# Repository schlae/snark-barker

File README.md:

# The Snark Barker - a SB 1.0 Clone

The Snark Barker is a 100% compatible clone of the famed SB 1.0 "Killer Card"
sound card from 1989. It implements all the features, including the digital
sound playback and recording, Ad Lib compatible synthesis, the joystick/MIDI
port, and the CMS chips (which are actually Philips SAA1099 synthesizer
devices).

All of the components are readily available. In the bill of materials,
Mouser part numbers are listed where they are available. Chips not available
from Mouser can be purchased from a variety of sources in China.

[Schematic](https://github.com/schlae/snark-barker/blob/master/SnarkBarker.pdf)

[Bill of Materials](https://github.com/schlae/snark-barker/blob/master/SnarkBarker.csv)

Please note that the 0.1" header pins are *not* listed on the BOM. They are
standard breakaway headers (both single and double row). Jumper shunts are
also not listed on the BOM.

[Fab files](https://github.com/schlae/snark-barker/blob/master/fab/SnarkBarker.zip)

Board dimensions are 9.1 x 4.2 inches. When ordering the board, you may want
to specify a card edge bevel (fairly cheap!) and selective gold plating
(expensive!) depending on your needs. The soldermask color can be whatever
you like, but hot pink is preferred.

## The Volume Knob
There don't seem to be any off-the-shelf knobs compatible with the Alps
potentiometer. You may be able to 3D print one based on the model below.
I'd recommend using a high-resolution SLA printer like the Formlabs Form 2.

Fasten it to the potentiometer using an M1.4x0.3mm thread, 6mm long screw
(McMaster-Carr part number 91800A036 or equivalent).

[Volume knob STEP model](https://github.com/schlae/snark-barker/blob/master/mech/vol_knob.zip)

Update: I've added a modified volume knob that may print better on FDM
printers.

[Volume knob STEP model, FDM version](https://github.com/schlae/snark-barker/blob/master/mech/vol_knob_fdm.zip)

## The ISA Card Bracket
The bracket specified in the BOM is a blank Keystone 9200 bracket. You will
need to punch or drill holes for the connectors. The KiCad board file has
detailed dimensions showing where to make the holes in the bracket.

I use a chassis nibbler tool to make the square slot for the volume knob as
well as the hole for the DA-15 joystick/MIDI connector. If you are rich,
Greenlee makes a punch for the DA-15 outline.

## The Firmware
There are two ways to get a programmed 80C51 chip for the Snark Barker. One
is to purchase a SB 2.0 DSP chip from China and put it in a 44-PLCC to
40-DIP adapter. This works fine and provides the largest feature set.

Another option is to buy a blank Atmel 89S51 (as listed in the BOM) and
program it with [this HEX file](https://github.com/schlae/snark-barker/blob/master/firmware/sb.hex).

## Assembly Notes
You may wish to socket the two CMS chips, the 80C51 microcontroller, and the
two Yamaha chips.

Be sure to add the 4.7K ohm bodge resistor on top of U5, running between
pins 4 and 14. (Shown below.)

For MIDI to work properly, you'll need to solder jumper wires on the headers
marked TXD and RXD (next to the SNARK BARKER logo). Originally these two 3-pin
headers may have been used as a debug port.

Be sure to place shunts in the jumpers marked DRQ1 and JP1, to enable DMA and
the joystick, respectively. Also place shunts to configure the I/O address and
IRQ.

## Testing and Diagnostics
Test your shiny new card using your favorite PC games, or use the [SBDIAG
program that I've written](https://github.com/schlae/snark-barker/tree/master/sbdiag).

## Other Notes
Like the original SB 1.0, the Snark Barker does not need a -5V rail.

## License
This work is licensed under a Creative Commons Attribution-ShareAlike 4.0
International License. See [https://creativecommons.org/licenses/by-sa/4.0/](https://creativecommons.org/licenses/by-sa/4.0/).

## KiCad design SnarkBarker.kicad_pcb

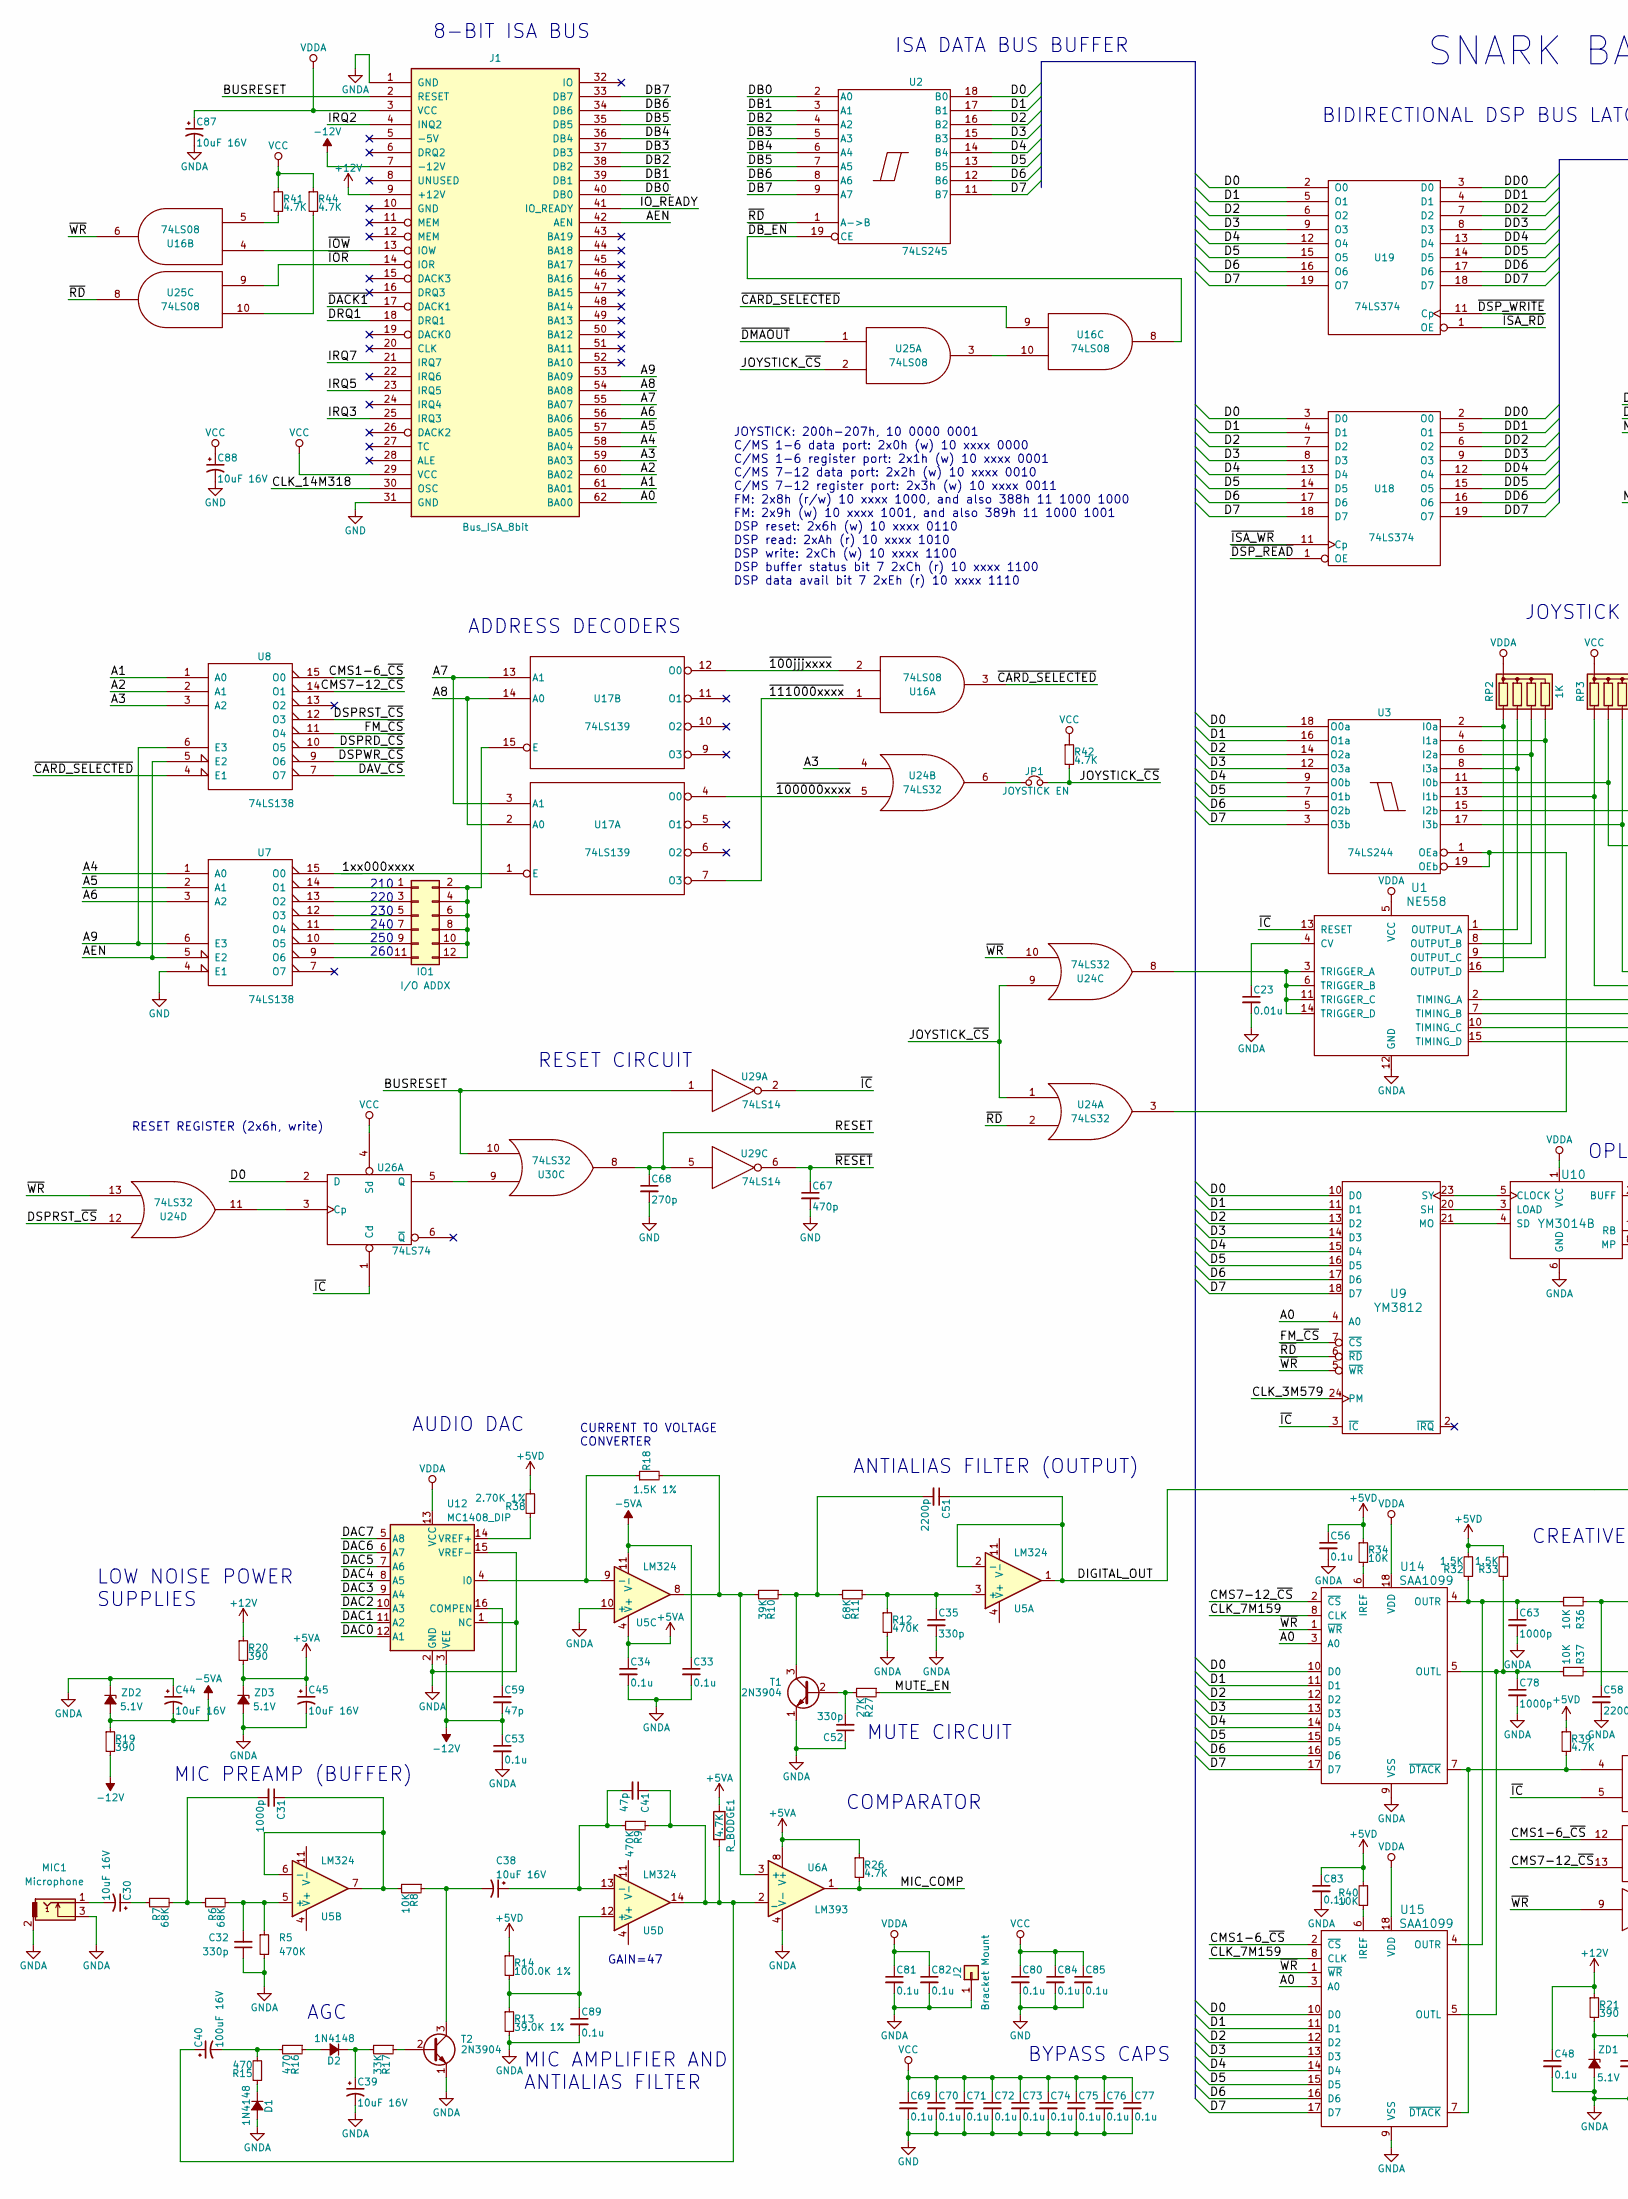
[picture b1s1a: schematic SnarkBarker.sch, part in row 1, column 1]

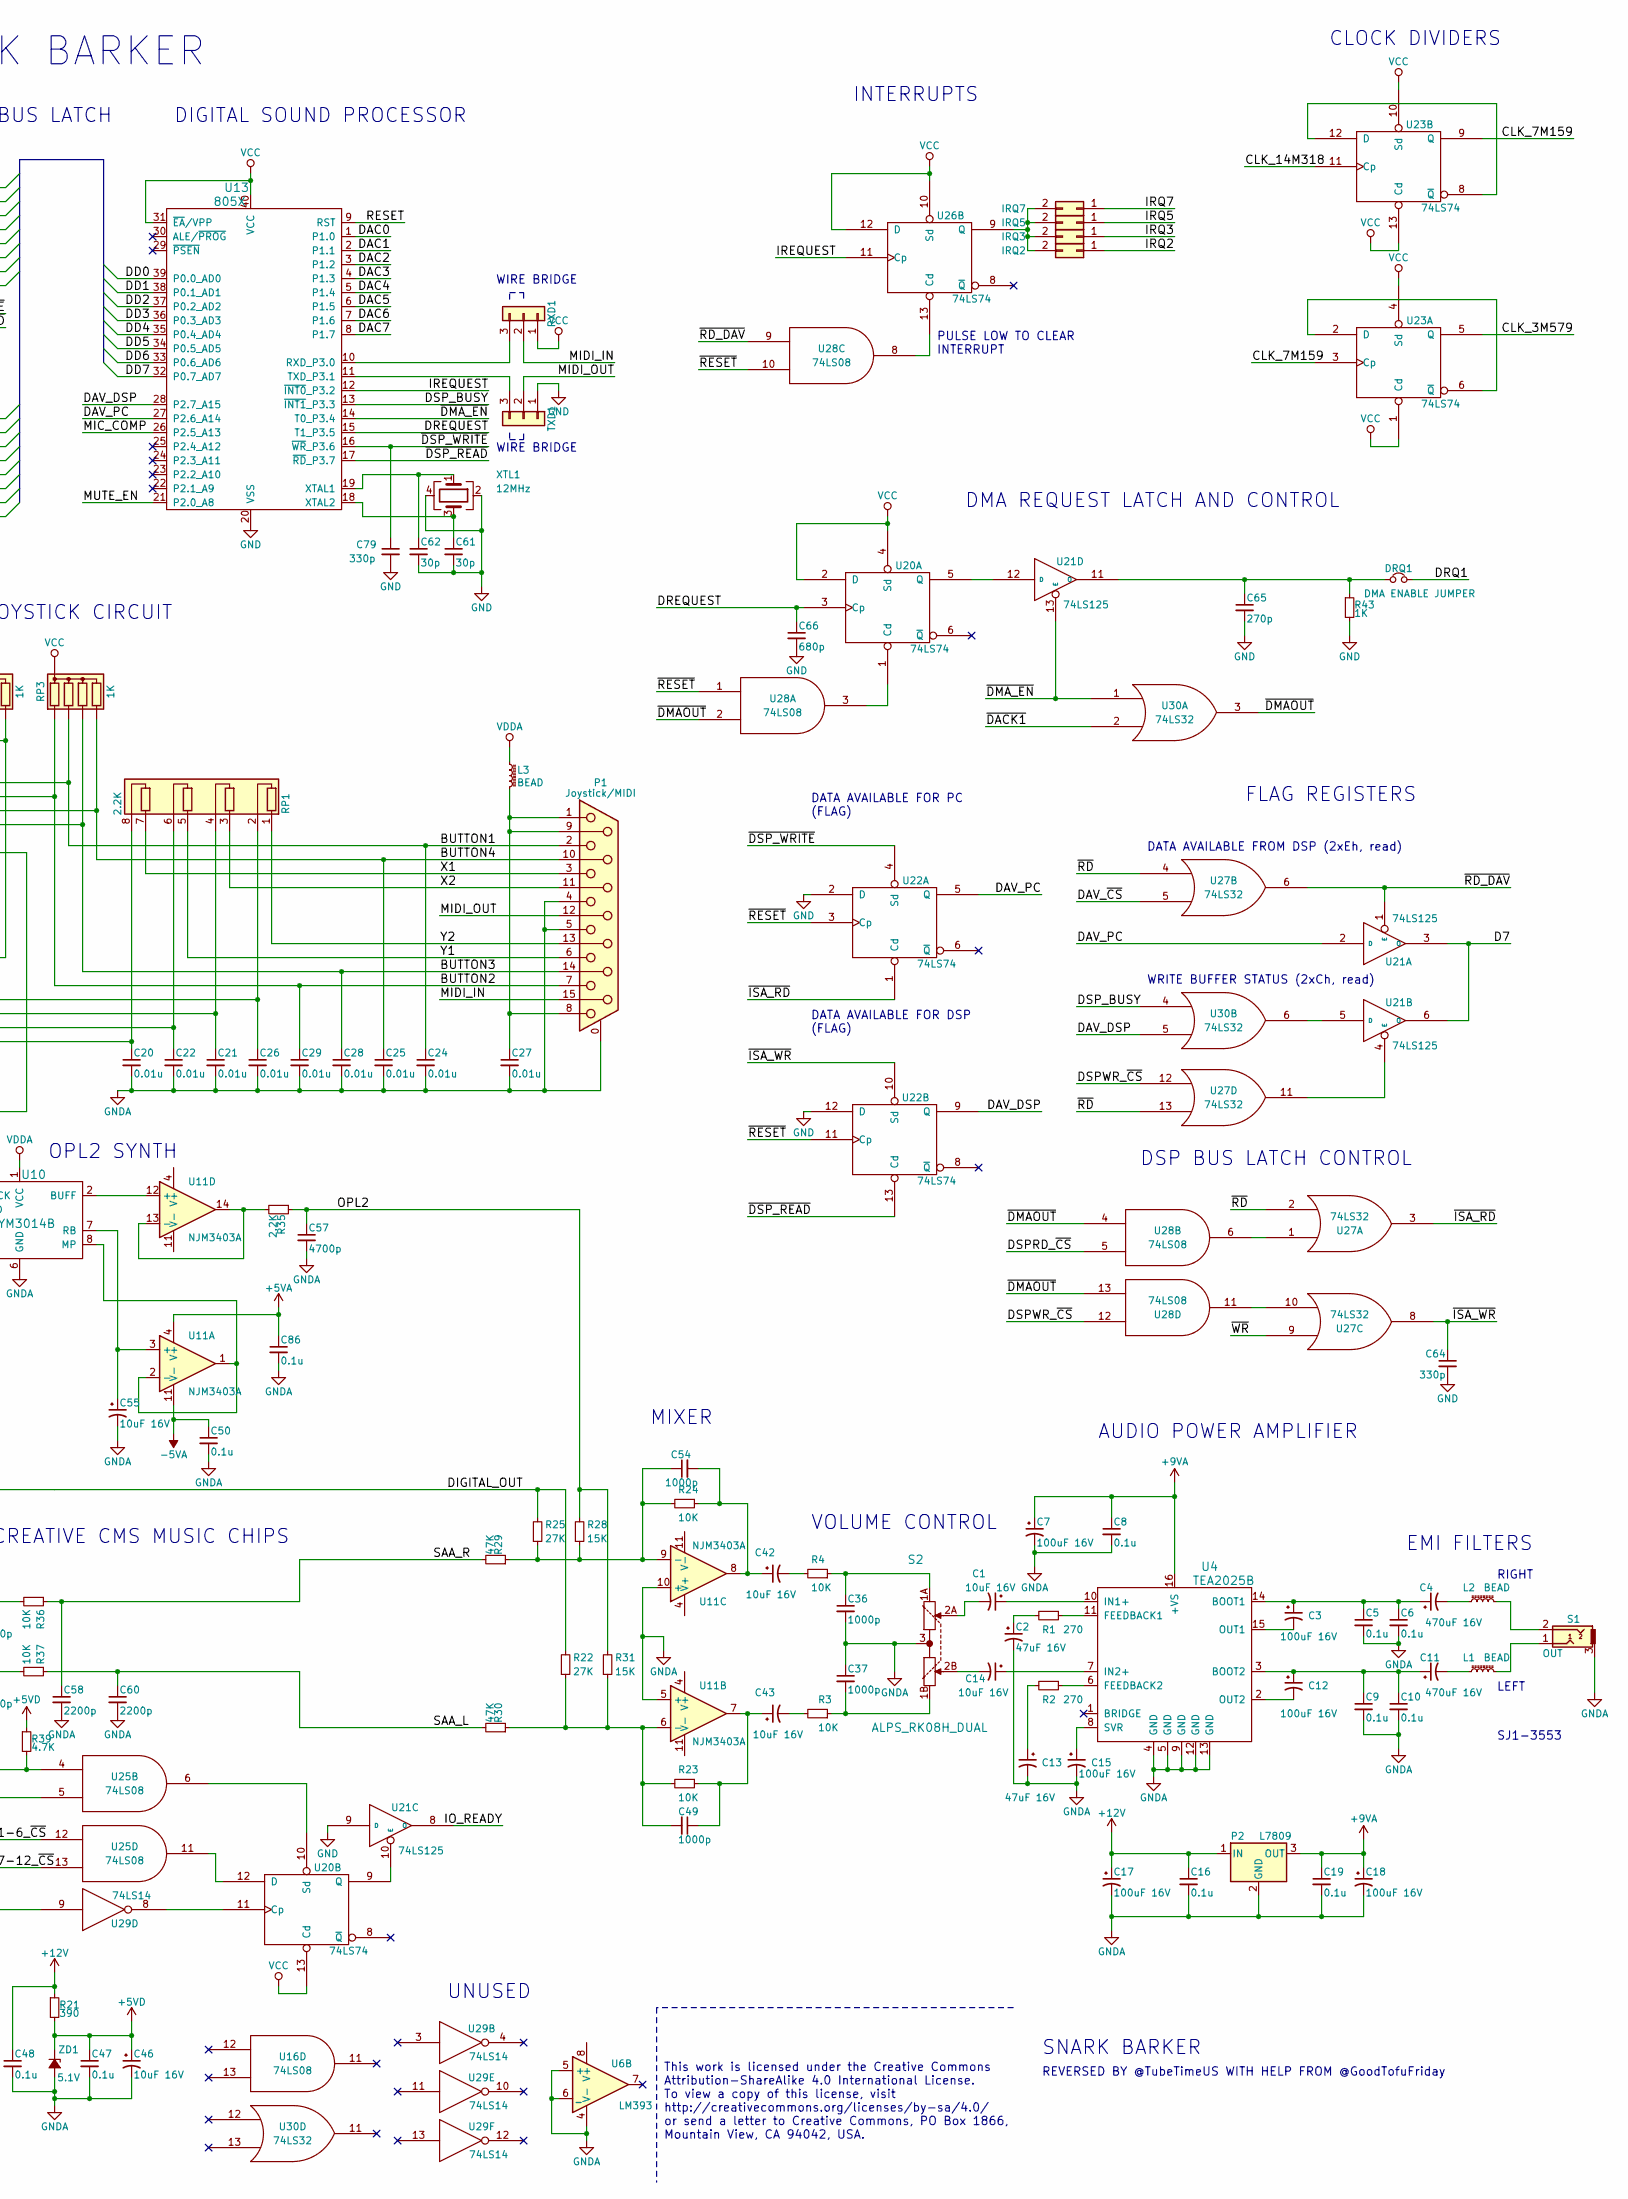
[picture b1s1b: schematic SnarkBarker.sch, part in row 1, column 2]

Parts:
C1, C14, C30, C38, C39, C42, C43, C44, C45, C46, C55, C87, C88: 10uF 16V; SB_C_RADIAL_75_150; Mouser 667-ECA-1CM100I
C2, C13: 47uF 16V; SB_C_RADIAL_75_150; Mouser 667-ECA-1CM470I
C3, C7, C12, C15, C17, C18, C40: 100uF 16V; SB_C_RADIAL_100_320; Mouser 667-ECA-1CM101I
C4, C11: 470uF 16V; SB_C_RADIAL_100_320; Mouser 667-ECA-1CM471B
C5, C6, C8, C9, C10, C16, C19, C33, C34, C47, C48, C50, C53, C56, C69, C70, C71, C72, C73, C74, C75, C76, C77, C80, C81, C82, C83, C84, C85, C86, C89: 0.1u; SB_C_AXIAL_275; Mouser 581-SA105E104M
C20, C21, C22, C23, C24, C25, C26, C27, C28, C29: 0.01u; SB_C_DISC_200; Mouser 810-FG28X7R1H103KNT0
C31, C36, C37, C49, C54, C63, C78: 1000p; SB_C_DISC_200; Mouser 810-FG28X7R1H102KNT6
C32, C35, C52, C64, C79: 330p; SB_C_DISC_200; Mouser 810-FG28C0G1H331JNT6
C41, C59: 47p; SB_C_DISC_200; Mouser 810-FG28C0G1H470JNT6
C51, C58, C60: 2200p; SB_C_DISC_200; Mouser 810-FG28X7R1H222KNT6
C57: 4700p; SB_C_DISC_200; Mouser 810-FG28C0G1H472JNT6
C61, C62: 30p; SB_C_DISC_200; Mouser 810-FG28C0G1H270JNT6
C65, C68: 270p; SB_C_DISC_200; Mouser 810-FG28C0G1H271JNT0
C66: 680p; SB_C_DISC_200; Mouser 810-FG28C0G1H681JNT6
C67: 470p; SB_C_DISC_200; Mouser 810-FG28C0G1H471JNT6
D1, D2: 1N4148; SB_D_AXIAL_400; Mouser 512-1N4148
DRQ1: DMA ENABLE JUMPER; SB_HDR_1X2
IO1: I/O ADDX; SB_HDR_2X6
IRQ2, IRQ3, IRQ5, IRQ7: Conn_02x01; SB_HDR_1X2
J1: Bus_ISA_8bit; BUS_PC
J2: Bracket Mount; SB_MH_125; Mouser 534-9200
JP1: JOYSTICK EN; SB_HDR_1X2
L1, L2, L3: BEAD; SB_L_AXIAL_500; Mouser 623-2743004111
MIC1: Microphone; SB_MJ-3536N; Mouser 490-MJ-3536N
P1: Joystick/MIDI; SB_DB15_152-3415; Mouser 152-3415
P2: L7809; SB_TO220; Mouser 511-L7809CV
R1, R2: 270; SB_R_AXIAL_400; Mouser 603-CFR-25JB-52-270R
R3, R4, R8, R23, R24, R34, R36, R37, R40: 10K; SB_R_AXIAL_400; Mouser 603-CFR-25JB-52-10K
R5, R9, R12: 470K; SB_R_AXIAL_400; Mouser 603-CFR-25JR-52470K
R6, R7, R11: 68K; SB_R_AXIAL_400; Mouser 603-CFR-25JB-52-68K
R10: 39K; SB_R_AXIAL_400; Mouser 603-CFR-25JB-52-39K
R13: 39.0K 1%; SB_R_AXIAL_400; Mouser 603-MFR-25FBF52-39K
R14: 100.0K 1%; SB_R_AXIAL_400; Mouser 603-MFR-25FBF52-100K
R15, R16: 470; SB_R_AXIAL_400; Mouser 603-CFR-25JB-52-470R
R17: 33K; SB_R_AXIAL_400; Mouser 603-CFR-25JB-52-33K
R18: 1.5K 1%; SB_R_AXIAL_400; Mouser 603-MFR-25FBF52-1K5
R19, R20, R21: 390; SB_R_AXIAL_400; Mouser 603-CFR-25JB-52-390R
R22, R25, R27: 27K; SB_R_AXIAL_400; Mouser 603-CFR-25JB-52-27K
R26, R39, R41, R42, R44: 4.7K; SB_R_AXIAL_400; Mouser 603-CFR-25JB-52-4K7
R28, R31: 15K; SB_R_AXIAL_400; Mouser 603-CFR-25JB-52-15K
R29, R30: 47K; SB_R_AXIAL_400; Mouser 603-CFR-25JB-52-47K
R32, R33: 1.5K; SB_R_AXIAL_400; Mouser 603-CFR-25JB-52-1K5
R35: 2.2K; SB_R_AXIAL_400; Mouser 603-CFR-25JB-52-2K2
R38: 2.70K 1%; SB_R_AXIAL_400; Mouser 603-MFR-25FBF52-2K7
R43: 1K; SB_R_AXIAL_400; Mouser 603-CFR-25JR-521K
RP1: 2.2K; SB_RP_4B; Mouser 652-4608X-AP2-222LF
RP2, RP3: 1K; SB_RP_4C; Mouser 652-4605X-AP1-102LF
RXD1: Conn_01x03; SB_HDR_1X3
R_BODGE1: 4.7K; Mouser 603-CFR-25JB-52-4K7
S1: OUT; SB_SJ1-3553; Mouser 490-SJ1-3553NG
S2: ALPS_RK08H_DUAL; SB_ALPS_RK08_DUAL; Mouser 688-RK08H12100F3
T1, T2: 2N3904; SB_TO92; Mouser 833-2N3904-AP
TXD1: Conn_01x03; SB_HDR_1X3
U1: NE558; SB_DIP16_300
U2: 74LS245; SB_DIP20_300; Mouser 595-SN74LS245N
U3: 74LS244; SB_DIP20_300; Mouser 595-SN74LS244N
U4: TEA2025B; SB_DIP16_300
U5: LM324; SB_DIP14_300; Mouser 512-LM324AN
U6: LM393; SB_DIP8_300; Mouser 595-LM393P
U7, U8: 74LS138; SB_DIP16_300; Mouser 595-SN74LS138NE4
U9: YM3812; SB_DIP24_600
U10: YM3014B; SB_DIP8_300
U11: NJM3403A; SB_DIP14_300; Mouser 513-NJM3403AD
U12: MC1408_DIP; SB_DIP16_300; Mouser 926-DAC0808LCN/NOPB
U13: 805X; SB_DIP40_600; Mouser 556-A89S51-24PU
U14, U15: SAA1099; SB_DIP18_300
U16, U25, U28: 74LS08; SB_DIP14_300; Mouser 595-SN74LS08N
U17: 74LS139; SB_DIP16_300; Mouser 595-SN74LS139AN
U18, U19: 74LS374; SB_DIP20_300; Mouser 595-SN74LS374N
U20, U22, U23, U26: 74LS74; SB_DIP14_300; Mouser 595-SN74LS74AN
U21: 74LS125; SB_DIP14_300; Mouser 595-SN74LS125AN
U24, U27, U30: 74LS32; SB_DIP14_300; Mouser 595-SN74LS32N
U29: 74LS14; SB_DIP14_300; Mouser 595-SN74LS14N
XTL1: 12MHz; SB_XTAL_HC49U_RA; Mouser 815-AB-12-B2
ZD1, ZD2, ZD3: 5.1V; SB_D_AXIAL_400_ALT; Mouser 78-1N5231B-TAP

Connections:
+5VA: C34.1, C45.1, C86.1, R20.2, R26.1, R_BODGE1.1, U5.4 (V+), U6.8 (V+), U11.4 (V+), ZD3.1 (K)
+5VD: C46.1, C47.1, C56.1, C83.1, R14.1, R21.2, R32.2, R33.2, R34.1, R38.2, R39.1, R40.1, ZD1.1 (K)
+9VA: C7.1, C8.1, C18.1, C19.1, P2.3 (OUT), U4.16 (+VS)
+12V: C16.1, C17.1, C48.1, J1.9 (+12V), P2.1 (IN), R20.1, R21.1
-5VA: C33.1, C44.2, C50.1, R19.1, U5.11 (V-), U11.11 (V-), ZD2.2 (A)
-12V: C53.1, C59.2, J1.7 (-12V), R19.2, U12.3 (VEE)
/1xx000xxxx: U7.15 (O0), U17.1 (E)
/A0: J1.62 (BA00), U9.4 (A0), U14.3 (A0), U15.3 (A0)
/A1: J1.61 (BA01), U8.1 (A0)
/A2: J1.60 (BA02), U8.2 (A1)
/A3: J1.59 (BA03), U8.3 (A2), U24.4
/A4: J1.58 (BA04), U7.1 (A0)
/A5: J1.57 (BA05), U7.2 (A1)
/A6: J1.56 (BA06), U7.3 (A2)
/A7: J1.55 (BA07), U17.3 (A1), U17.13 (A1)
/A8: J1.54 (BA08), U17.2 (A0), U17.14 (A0)
/A9: J1.53 (BA09), U7.6 (E3), U8.6 (E3)
/AEN: J1.42 (AEN), U7.5 (E2), U8.5 (E2)
/BUSRESET: J1.2 (RESET), U29.1, U30.10
/BUTTON1: C24.1, P1.2, RP3.3 (R2), U3.11 (I0b)
/BUTTON2: C29.1, P1.7, RP3.2 (R1), U3.13 (I1b)
/BUTTON3: C28.1, P1.14, RP3.4 (R3), U3.17 (I3b)
/BUTTON4: C25.1, P1.10, RP3.5 (R4), U3.15 (I2b)
/CLK_3M579: U9.24 (PM), U23.5 (Q)
/CLK_7M159: U14.8 (CLK), U15.8 (CLK), U23.3 (Cp), U23.9 (Q)
/CLK_14M318: J1.30 (OSC), U23.11 (Cp)
/CMS1-6_~CS: U8.15 (O0), U15.2 (~CS), U25.12
/CMS7-12_~CS: U8.14 (O1), U14.2 (~CS), U25.13
/D0: U2.18 (B0), U3.18 (O0a), U9.10 (D0), U14.10 (D0), U15.10 (D0), U18.3 (D0), U19.2 (O0), U26.2 (D)
/D1: U2.17 (B1), U3.16 (O1a), U9.11 (D1), U14.11 (D1), U15.11 (D1), U18.4 (D1), U19.5 (O1)
/D2: U2.16 (B2), U3.14 (O2a), U9.13 (D2), U14.12 (D2), U15.12 (D2), U18.7 (D2), U19.6 (O2)
/D3: U2.15 (B3), U3.12 (O3a), U9.14 (D3), U14.13 (D3), U15.13 (D3), U18.8 (D3), U19.9 (O3)
/D4: U2.14 (B4), U3.9 (O0b), U9.15 (D4), U14.14 (D4), U15.14 (D4), U18.13 (D4), U19.12 (O4)
/D5: U2.13 (B5), U3.7 (O1b), U9.16 (D5), U14.15 (D5), U15.15 (D5), U18.14 (D5), U19.15 (O5)
/D6: U2.12 (B6), U3.5 (O2b), U9.17 (D6), U14.16 (D6), U15.16 (D6), U18.17 (D6), U19.16 (O6)
/D7: U2.11 (B7), U3.3 (O3b), U9.18 (D7), U14.17 (D7), U15.17 (D7), U18.18 (D7), U19.19 (O7), U21.3 (O), U21.6 (O)
/DAC0: U12.12 (A1), U13.1 (P1.0)
/DAC1: U12.11 (A2), U13.2 (P1.1)
/DAC2: U12.10 (A3), U13.3 (P1.2)
/DAC3: U12.9 (A4), U13.4 (P1.3)
/DAC4: U12.8 (A5), U13.5 (P1.4)
/DAC5: U12.7 (A6), U13.6 (P1.5)
/DAC6: U12.6 (A7), U13.7 (P1.6)
/DAC7: U12.5 (A8), U13.8 (P1.7)
/DAV_DSP: U13.28 (P2.7_A15), U22.9 (Q), U30.5
/DAV_PC: U13.27 (P2.6_A14), U21.2 (D), U22.5 (Q)
/DAV_~CS: U8.7 (O7), U27.5
/DB0: J1.40 (DB0), U2.2 (A0)
/DB1: J1.39 (DB1), U2.3 (A1)
/DB2: J1.38 (DB2), U2.4 (A2)
/DB3: J1.37 (DB3), U2.5 (A3)
/DB4: J1.36 (DB4), U2.6 (A4)
/DB5: J1.35 (DB5), U2.7 (A5)
/DB6: J1.34 (DB6), U2.8 (A6)
/DB7: J1.33 (DB7), U2.9 (A7)
/DD0: U13.39 (P0.0_AD0), U18.2 (O0), U19.3 (D0)
/DD1: U13.38 (P0.1_AD1), U18.5 (O1), U19.4 (D1)
/DD2: U13.37 (P0.2_AD2), U18.6 (O2), U19.7 (D2)
/DD3: U13.36 (P0.3_AD3), U18.9 (O3), U19.8 (D3)
/DD4: U13.35 (P0.4_AD4), U18.12 (O4), U19.13 (D4)
/DD5: U13.34 (P0.5_AD5), U18.15 (O5), U19.14 (D5)
/DD6: U13.33 (P0.6_AD6), U18.16 (O6), U19.17 (D6)
/DD7: U13.32 (P0.7_AD7), U18.19 (O7), U19.18 (D7)
/DIGITAL_OUT: C51.1, R22.2, R25.2, U5.1, U5.2 (-)
/DREQUEST: C66.1, U13.15 (T1_P3.5), U20.3 (Cp)
/DRQ1: DRQ1.2, J1.18 (DRQ1)
/DSPRD_~CS: U8.10 (O5), U28.5
/DSPRST_~CS: U8.12 (O3), U24.12
/DSPWR_~CS: U8.9 (O6), U27.12, U28.12
/DSP_BUSY: U13.13 (~INT1~_P3.3), U30.4
/FM_~CS: U8.11 (O4), U9.7 (~CS)
/IO_READY: J1.41 (IO_READY), U21.8 (O)
/IREQUEST: U13.12 (~INT0~_P3.2), U26.11 (Cp)
/IRQ2: IRQ2.1, J1.4 (INQ2)
/IRQ3: IRQ3.1, J1.25 (IRQ3)
/IRQ5: IRQ5.1, J1.23 (IRQ5)
/IRQ7: IRQ7.1, J1.21 (IRQ7)
/JOYSTICK_~CS: JP1.2, R42.2, U24.1, U24.9, U25.2
/MIC_COMP: R26.2, U6.1, U13.26 (P2.5_A13)
/MIDI_IN: P1.15, RXD1.2
/MIDI_OUT: P1.12, TXD1.2
/MUTE_EN: R27.1, U13.21 (P2.0_A8)
/OPL2: C57.1, R28.2, R31.2, R35.1
/RESET: C68.1, U13.9 (RST), U29.5, U30.8
/SAA_L: C60.1, R30.2, R37.1
/SAA_R: C58.1, R29.2, R36.1
/X1: P1.3, RP1.7 (R4.1)
/X2: P1.11 (P111), RP1.3 (R2.1)
/Y1: P1.6, RP1.5 (R3.1)
/Y2: P1.13, RP1.1 (R1.1)
/~100jjjxxxx: U16.2, U17.12 (O0)
/~100000xxxx: U17.4 (O0), U24.5
/~111000xxxx: U16.1, U17.7 (O3)
/~CARD_SELECTED: U8.4 (E1), U16.3, U16.9
/~DACK1: J1.17 (DACK1), U30.2
/~DB_EN: U2.19 (CE), U16.8
/~DMAOUT: U25.1, U28.2, U28.4, U28.13, U30.3
/~DMA_EN: U13.14 (T0_P3.4), U21.13 (E), U30.1
/~DSP_READ: U13.17 (~RD~_P3.7), U18.1 (OE), U22.13 (Cd)
/~DSP_WRITE: C79.1, U13.16 (~WR~_P3.6), U19.11 (Cp), U22.4 (Sd)
/~IC: U1.13 (RESET), U9.3 (~IC), U25.5, U26.1 (Cd), U29.2
/~IOR: J1.14 (IOR), U25.9
/~IOW: J1.13 (IOW), U16.4
/~ISA_RD: U19.1 (OE), U22.1 (Cd), U27.3
/~ISA_WR: C64.1, U18.11 (Cp), U22.10 (Sd), U27.8
/~RD: U2.1 (A->B), U9.6 (~RD), U24.2, U25.8, U27.2, U27.4, U27.13
/~RD_DAV: U21.1 (E), U27.6, U28.9
/~RESET: C67.1, U22.3 (Cp), U22.11 (Cp), U28.1, U28.10, U29.6
/~WR: U9.5 (~WR), U14.1 (~WR), U15.1 (~WR), U16.6, U24.10, U24.13, U27.9, U29.9
GND: C61.2, C62.2, C64.2, C65.2, C66.2, C67.2, C68.2, C69.2, C70.2, C71.2, C72.2, C73.2, C74.2, C75.2, C76.2, C77.2, C79.2, C80.2, C84.2, C85.2, C88.2, J1.31 (GND), R43.2, TXD1.1, U2.10 (GND), U3.10 (GND), U7.4 (E1), U7.8 (GND), U8.8 (GND), U9.12 (GND), U13.20 (VSS), U16.7 (GND), U17.8 (GND), U18.10 (GND), U19.10 (GND), U20.7 (GND), U21.7 (GND), U21.9 (D), U22.2 (D), U22.7 (GND), U22.12 (D), U23.7 (GND), U24.7 (GND), U25.7 (GND), U26.7 (GND), U27.7 (GND), U28.7 (GND), U29.7 (GND), U30.7 (GND), XTL1.2, XTL1.4
GNDA: C2.2, C5.2, C6.2, C7.2, C8.2, C9.2, C10.2, C13.2, C15.2, C16.2, C17.2, C18.2, C19.2, C20.2, C21.2, C22.2, C23.2, C24.2, C25.2, C26.2, C27.2, C28.2, C29.2, C32.1, C33.2, C34.2, C35.2, C36.2, C37.1, C39.2, C44.1, C45.2, C46.2, C47.2, C48.2, C50.2, C52.1, C53.2, C55.2, C56.2, C57.2, C58.2, C60.2, C63.2, C78.2, C81.2, C82.2, C83.2, C86.2, C87.2, C89.2, D1.2 (A), J1.1 (GND), J2.1, MIC1.2, MIC1.3, P1.0 (PAD), P1.4, P1.5, P2.2 (GND), R5.2, R12.2, R13.2, S1.3, S2.3, T1.1 (E), T2.1 (E), U1.12 (GND), U4.4 (GND), U4.5 (GND), U4.9 (GND), U4.12 (GND), U4.13 (GND), U5.10 (+), U6.4 (V-), U6.5 (+), U6.6 (_), U10.6 (GND), U11.5 (+), U11.10 (+), U12.1 (NC), U12.2 (GND), U12.15 (VREF-), U14.9 (VSS), U15.9 (VSS), ZD1.2 (A), ZD2.1 (K), ZD3.2 (A)
unnamed: C1.1, U4.10 (IN1+)
unnamed: C1.2, S2.2A
unnamed: C2.1, R1.2
unnamed: C3.1, C4.1, C5.1, C6.1, U4.14 (BOOT1)
unnamed: C3.2, U4.15 (OUT1)
unnamed: C4.2, L2.1
unnamed: C9.1, C10.1, C11.1, C12.1, U4.3 (BOOT2)
unnamed: C11.2, L1.1
unnamed: C12.2, U4.2 (OUT2)
unnamed: C13.1, R2.2
unnamed: C14.1, U4.7 (IN2+)
unnamed: C14.2, S2.2B
unnamed: C15.1, U4.8 (SVR)
unnamed: C20.1, RP1.8 (R4.2), U1.15 (TIMING_D)
unnamed: C21.1, RP1.4 (R2.2), U1.7 (TIMING_B)
unnamed: C22.1, RP1.6 (R3.2), U1.10 (TIMING_C)
unnamed: C23.1, U1.4 (CV)
unnamed: C26.1, RP1.2 (R1.2), U1.2 (TIMING_A)
unnamed: C27.1, L3.2, P1.1, P1.8, P1.9
unnamed: C30.1, R7.1
unnamed: C30.2, MIC1.1
unnamed: C31.1, R8.2, U5.6 (-), U5.7
unnamed: C31.2, R6.1, R7.2
unnamed: C32.2, R5.1, R6.2, U5.5 (+)
unnamed: C35.1, R11.1, R12.1, U5.3 (+)
unnamed: C36.1, R4.1, S2.1A
unnamed: C37.2, R3.1, S2.1B
unnamed: C38.1, C41.2, R9.2, U5.13 (-)
unnamed: C38.2, R8.1, T2.3 (C)
unnamed: C39.1, D2.1 (K), R17.2
unnamed: C40.1, C41.1, R9.1, R_BODGE1.2, U5.14, U6.2 (_)
unnamed: C40.2, R15.2, R16.2
unnamed: C42.1, C54.2, R24.1, U11.8
unnamed: C42.2, R4.2
unnamed: C43.1, C49.1, R23.1, U11.7
unnamed: C43.2, R3.2
unnamed: C49.2, R22.1, R23.2, R30.1, R31.1, U11.6 (-)
unnamed: C51.2, R10.1, R11.2, T1.3 (C)
unnamed: C52.2, R27.2, T1.2 (B)
unnamed: C54.1, R24.2, R25.1, R28.1, R29.1, U11.9 (-)
unnamed: C55.1, U10.7 (RB), U11.3 (+)
unnamed: C59.1, U12.16 (COMPEN)
unnamed: C61.1, U13.18 (XTAL2), XTL1.3
unnamed: C62.1, U13.19 (XTAL1), XTL1.1
unnamed: C63.1, R32.1, R36.2, U14.4 (OUTR), U15.4 (OUTR)
unnamed: C65.1, DRQ1.1, R43.1, U21.11 (O)
unnamed: C78.1, R33.1, R37.2, U14.5 (OUTL), U15.5 (OUTL)
unnamed: C89.1, R13.1, R14.2, U5.12 (+)
unnamed: D1.1 (K), R15.1
unnamed: D2.2 (A), R16.1
unnamed: IO1.1, U7.14 (O1)
unnamed: IO1.3, U7.13 (O2)
unnamed: IO1.5, U7.12 (O3)
unnamed: IO1.7, U7.11 (O4)
unnamed: IO1.9, U7.10 (O5)
unnamed: IO1.2, IO1.4, IO1.6, IO1.8, IO1.10, IO1.12, U17.15 (E)
unnamed: IO1.11, U7.9 (O6)
unnamed: IRQ2.2, IRQ3.2, IRQ5.2, IRQ7.2, U26.9 (Q)
unnamed: JP1.1, U24.6
unnamed: L1.2, S1.1
unnamed: L2.2, S1.2
unnamed: R1.1, U4.11 (FEEDBACK1)
unnamed: R2.1, U4.6 (FEEDBACK2)
unnamed: R10.2, R18.2, U5.8, U6.3 (+)
unnamed: R17.1, T2.2 (B)
unnamed: R18.1, U5.9 (-), U12.4 (I0)
unnamed: R34.2, U14.6 (IREF)
unnamed: R35.2, U11.13 (-), U11.14
unnamed: R38.1, U12.14 (VREF+)
unnamed: R39.2, U14.7 (~DTACK), U15.7 (~DTACK), U25.4
unnamed: R40.2, U15.6 (IREF)
unnamed: R41.2, U16.5
unnamed: R44.2, U25.10
unnamed: RP2.2 (R1), U1.16 (OUTPUT_D), U3.2 (I0a)
unnamed: RP2.3 (R2), U1.1 (OUTPUT_A), U3.8 (I3a)
unnamed: RP2.4 (R3), U1.8 (OUTPUT_B), U3.6 (I2a)
unnamed: RP2.5 (R4), U1.9 (OUTPUT_C), U3.4 (I1a)
unnamed: RXD1.3, U13.10 (RXD_P3.0)
unnamed: TXD1.3, U13.11 (TXD_P3.1)
unnamed: U1.3 (TRIGGER_A), U1.6 (TRIGGER_B), U1.11 (TRIGGER_C), U1.14 (TRIGGER_D), U24.8
unnamed: U10.2 (BUFF), U11.12 (+)
unnamed: U9.20 (SH), U10.3 (LOAD)
unnamed: U9.21 (MO), U10.4 (SD)
unnamed: U9.23 (SY), U10.5 (CLOCK)
unnamed: U10.8 (MP), U11.1, U11.2 (-)
unnamed: U16.10, U25.3
unnamed: U20.1 (Cd), U28.3
unnamed: U20.5 (Q), U21.12 (D)
unnamed: U20.9 (Q), U21.10 (E)
unnamed: U20.10 (Sd), U25.6
unnamed: U20.11 (Cp), U29.8
unnamed: U20.12 (D), U25.11
unnamed: U21.4 (E), U27.11
unnamed: U21.5 (D), U30.6
unnamed: U23.2 (D), U23.6 (~Q)
unnamed: U23.8 (~Q), U23.12 (D)
unnamed: U3.1 (OEa), U3.19 (OEb), U24.3
unnamed: U24.11, U26.3 (Cp)
unnamed: U26.5 (Q), U30.9
unnamed: U26.13 (Cd), U28.8
unnamed: U27.1, U28.6
unnamed: U27.10, U28.11
VCC: C69.1, C70.1, C71.1, C72.1, C73.1, C74.1, C75.1, C76.1, C77.1, C80.1, C84.1, C85.1, C88.1, J1.29 (VCC), R41.1, R42.1, R44.1, RP3.1 (common), RXD1.1, U2.20 (VCC), U3.20 (VCC), U7.16 (VCC), U8.16 (VCC), U9.1 (VCC), U13.31 (~EA~/VPP), U13.40 (VCC), U16.14 (VCC), U17.16 (VCC), U18.20 (VCC), U19.20 (VCC), U20.2 (D), U20.4 (Sd), U20.13 (Cd), U20.14 (VCC), U21.14 (VCC), U22.14 (VCC), U23.1 (Cd), U23.4 (Sd), U23.10 (Sd), U23.13 (Cd), U23.14 (VCC), U24.14 (VCC), U25.14 (VCC), U26.4 (Sd), U26.10 (Sd), U26.12 (D), U26.14 (VCC), U27.14 (VCC), U28.14 (VCC), U29.14 (VCC), U30.14 (VCC)
VDDA: C81.1, C82.1, C87.1, J1.3 (VCC), L3.1, RP2.1 (common), U1.5 (VCC), U10.1 (VCC), U12.13 (VCC), U14.18 (VDD), U15.18 (VDD)

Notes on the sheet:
BYPASS CAPS
210 220 230 240 250 260
AGC
MIC PREAMP (BUFFER)
MIC AMPLIFIER AND ANTIALIAS FILTER
GAIN=47
CURRENT TO VOLTAGE CONVERTER
AUDIO DAC
MUTE CIRCUIT
ANTIALIAS FILTER (OUTPUT)
COMPARATOR
MIXER
VOLUME CONTROL
AUDIO POWER AMPLIFIER
EMI FILTERS
LEFT
RIGHT
LOW NOISE POWER SUPPLIES
OPL2 SYNTH
CREATIVE CMS MUSIC CHIPS
JOYSTICK CIRCUIT
CLOCK DIVIDERS
PULSE LOW TO CLEAR INTERRUPT
JOYSTICK: 200h-207h, 10 0000 0001 C/MS 1-6 data port: 2x0h (w) 10 xxxx 0000 C/MS 1-6 register port: 2x1h (w) 10 xxxx 0001 C/MS 7-12 data port: 2x2h (w) 10 xxxx 0010 C/MS 7-12 register port: 2x3h (w) 10 xxxx 0011 FM: 2x8h (r/w) 10 xxxx 1000, and also 388h 11 1000 1000 FM: 2x9h (w) 10 xxxx 1001, and 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
FLAG REGISTERS
INTERRUPTS
DMA REQUEST LATCH AND CONTROL
ISA DATA BUS BUFFER
RESET CIRCUIT
DATA AVAILABLE FOR PC (FLAG)
DATA AVAILABLE FOR DSP (FLAG)
DATA AVAILABLE FROM DSP (2xEh, read)
WRITE BUFFER STATUS (2xCh, read)
RESET REGISTER (2x6h, write)
8-BIT ISA BUS
DIGITAL SOUND PROCESSOR
BIDIRECTIONAL DSP BUS LATCH
DSP BUS LATCH CONTROL
ADDRESS DECODERS
UNUSED

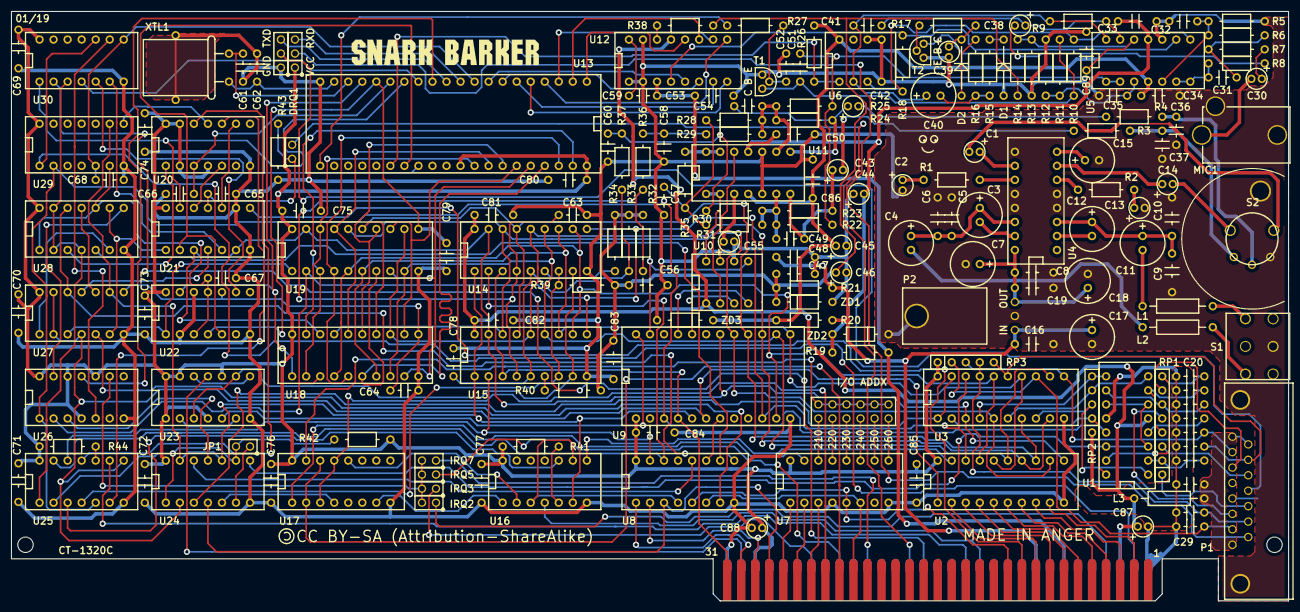
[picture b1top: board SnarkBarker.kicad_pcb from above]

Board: 2 copper layers, 231.1 x 106.7 mm, 193 parts (0 on the bottom side), 215 nets.

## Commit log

2019-01-18 Initial empty commit
2019-01-19 Formatting
2019-01-26 Make compatible with kitspace.org
2019-03-19 Added FDM version of volume knob
2019-10-20 Added initial version of firmware spec
2019-10-20 Fix typo
2020-08-09 Added initial version of SBDIAG
2020-08-13 Added CMS chip support. Fixed menu crash.
2020-08-13 Added CMS test documentation.
2020-11-08 Fix a typo
2022-01-04 Explicitly disable noise generator
    This should close issue #8
2022-01-05 Rebuilt SBDIAG.EXE
2023-02-15 sbdiag: wait_write() now reads 8 bits instead of 16
2023-03-09 Swap out obsolete parts P1 and U5

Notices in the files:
SnarkBarker.kicad_pcb:
Copyright (C) 2018 Eric Schlaepfer
CC BY-SA (Attribution-ShareAlike)
SnarkBarker.sch:
This work is licensed under the Creative Commons
http://creativecommons.org/licenses/by-sa/4.0
or send a letter to Creative Commons, PO Box 1866,
Mountain View, CA 94042, USA.
